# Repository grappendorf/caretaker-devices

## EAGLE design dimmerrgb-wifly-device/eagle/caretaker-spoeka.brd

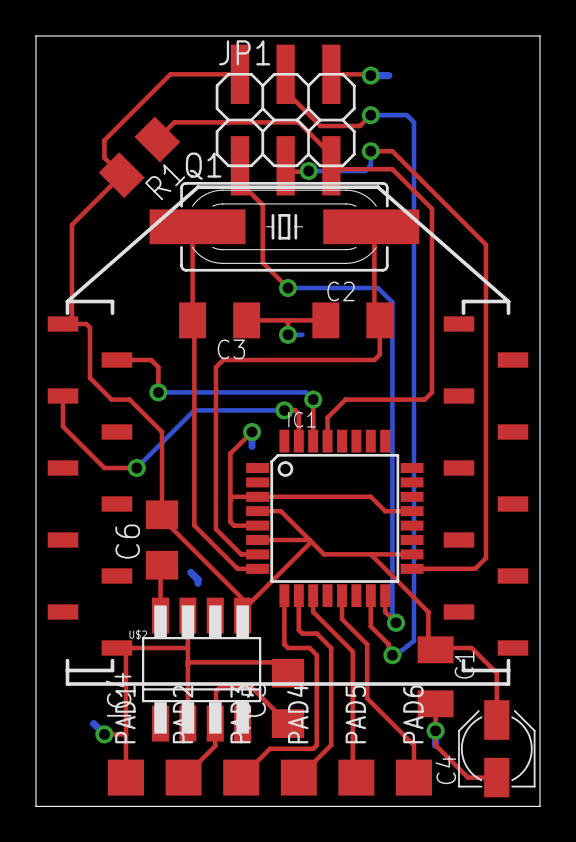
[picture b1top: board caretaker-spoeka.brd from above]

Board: 2 copper layers, 28.0 x 42.8 mm, 18 parts (0 on the bottom side), 16 nets.

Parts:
C1: 100n; C1206K
C2, C3: 22p; C1206K
C4: 1u/16V; PANASONIC_B
C5: 100n; C1206
C6: 10p; C1206
IC1: ATMEGA168; TQFP32-08
IC4: ZLDO330; SM8
JP1: 2X03SMD
PAD1, PAD2, PAD3, PAD4, PAD5, PAD6: PAD-SMD20S; SMD20S
Q1: 16MHz; HC49UP
R1: 10k; M1206
U$2: WIFLY-SMD

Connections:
+3V3: C1.1, C4.+, C6.2, IC1.4, IC1.6, IC1.18, IC4.5, JP1.2, R1.2, U$2.1
BUTTON: IC1.11, PAD5.PAD
GND: C1.2, C2.1, C3.1, C4.-, C5.2, IC1.3, IC1.5, IC1.21, IC4.2, IC4.7, JP1.6, PAD1.PAD, U$2.10
LED_BLUE: IC1.13, PAD6.PAD
LED_GREEN: IC1.10, PAD4.PAD
LED_RED: IC1.9, PAD3.PAD
MISO: IC1.16, JP1.1
MOSI: IC1.15, JP1.4
unnamed: C2.2, IC1.7, Q1.2
unnamed: C3.2, IC1.8, Q1.1
unnamed: C6.1, IC4.8
POW: C5.1, IC4.3, PAD2.PAD
RESET: IC1.29, JP1.5, R1.1
RXD: IC1.30, U$2.2
SCK: IC1.17, JP1.3
TXD: IC1.31, U$2.3

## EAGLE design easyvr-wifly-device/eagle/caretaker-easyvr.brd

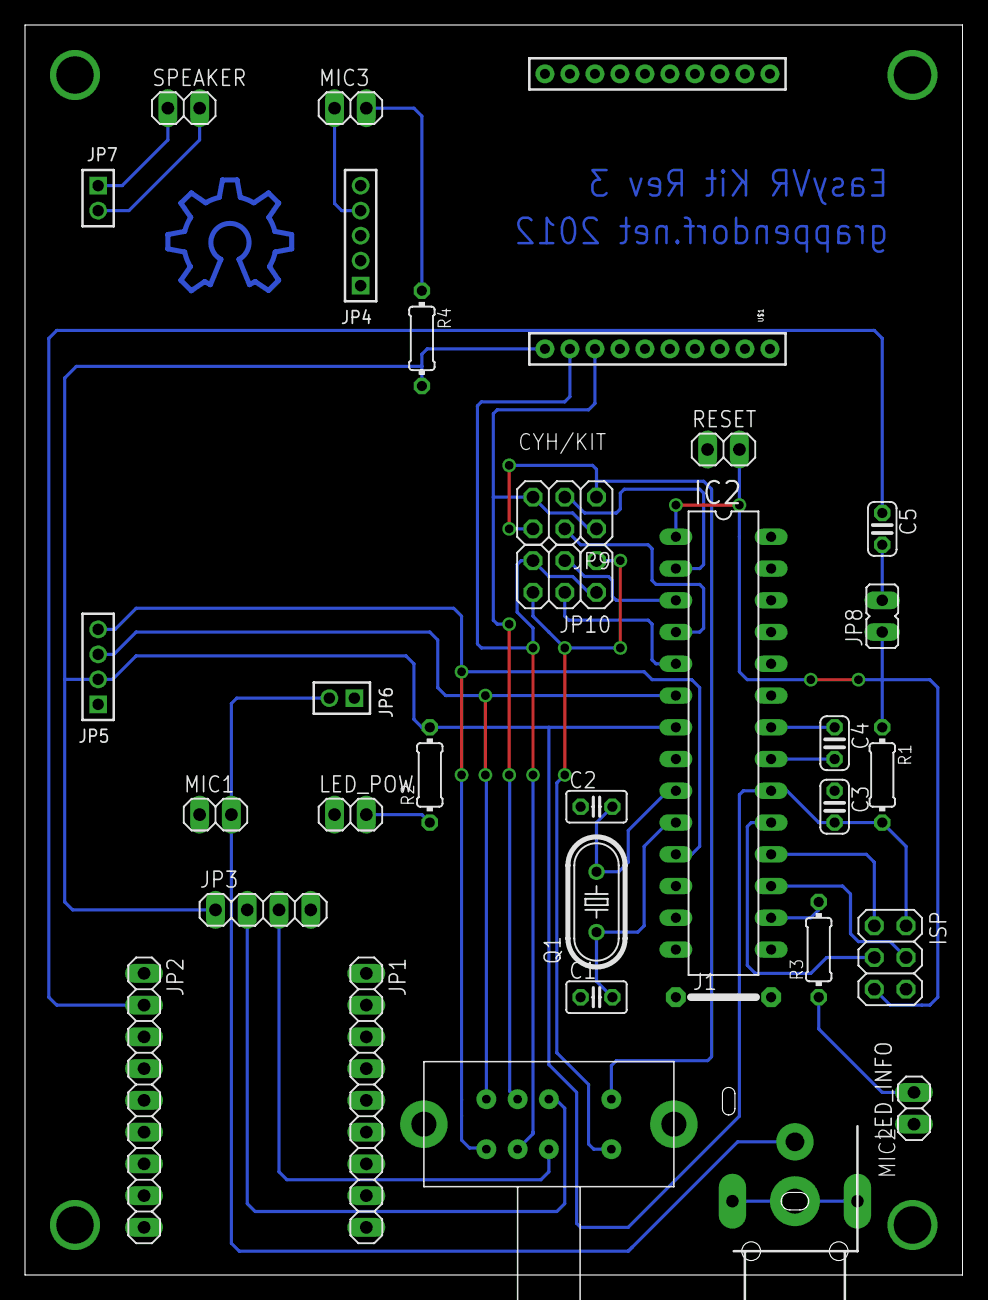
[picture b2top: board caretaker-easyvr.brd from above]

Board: 2 copper layers, 75.0 x 100.0 mm, 33 parts (0 on the bottom side), 31 nets.

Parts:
C1, C2: 22p; C025-025X050
C3, C4, C5: 100n; C025-024X044
IC2: ATmega168-20PU; DIL28-3
ISP: 2X03
J1: J7MM; 07
JP1, JP2: 1X09
JP3: 1X04
JP4: 1X05M
JP5: 1X04M
JP6, JP7: 1X02M
JP8: JP1
JP9, JP10: 2X03
LED_INFO: 1X02
LED_POW: 1X02
LOGO2: OSHW_LOGO_10MILX0350-NT-BOTTOM; OSHW_10X350_NOTEXT_BOTTOM
MIC1, MIC3: 1X02
MIC2: CINCH1
Q1: 16MHz; HC49U-V
R1: 10k; 0204/7
R2, R3: 1k; 0204/7
R4: 100; 0204/7
RESET: 1X02
SPEAKER: 1X02
U$1: WIFLY-TH
U$2: CONRAD-708038

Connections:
+3V3: C3.2, IC2.7, IC2.20, ISP.2, JP3.1, JP5.2, R1.2, R2.2, R4.2, U$1.1
AVR_RXD: JP9.1, JP9.6, U$2.C1
AVR_TXD: JP10.1, JP10.6, U$2.C2
EASYVR_RXD: IC2.6, JP5.3, U$2.A1
EASYVR_TXD: IC2.11, JP5.4, U$2.A2
GND: C1.1, C2.1, C3.1, C4.1, IC2.8, IC2.22, ISP.6, J1.1, J1.2, JP3.4, JP5.1, JP6.1, LED_INFO.1, LED_POW.1, MIC1.1, MIC2.T, MIC2.X1, MIC2.X2, RESET.1, U$1.10
LED_INFO: IC2.16, R3.2
MIC: JP6.2, MIC1.2, MIC2.S
unnamed: C2.2, IC2.9, Q1.2
unnamed: C1.2, IC2.10, Q1.1
unnamed: C4.2, IC2.21
unnamed: IC2.18, ISP.1
unnamed: IC2.19, ISP.3
unnamed: C5.2, JP8.2
unnamed: C5.1, JP2.2
unnamed: LED_POW.2, R2.1
unnamed: LED_INFO.2, R3.1
unnamed: JP7.2, SPEAKER.2
unnamed: JP7.1, SPEAKER.1
unnamed: JP4.4, MIC3.1
unnamed: MIC3.2, R4.1
unnamed: IC2.2, JP9.3
unnamed: IC2.4, JP9.4
unnamed: IC2.3, JP10.3
unnamed: IC2.5, JP10.4
unnamed: IC2.17, ISP.4
RESET: IC2.1, ISP.5, JP8.1, R1.1, RESET.2
USB_RXD: JP3.3, U$2.X2
USB_TXD: JP3.2, U$2.X1
WIFI_RXD: JP9.2, JP9.5, U$1.3, U$2.B1
WIFI_TXD: JP10.2, JP10.5, U$1.2, U$2.B2

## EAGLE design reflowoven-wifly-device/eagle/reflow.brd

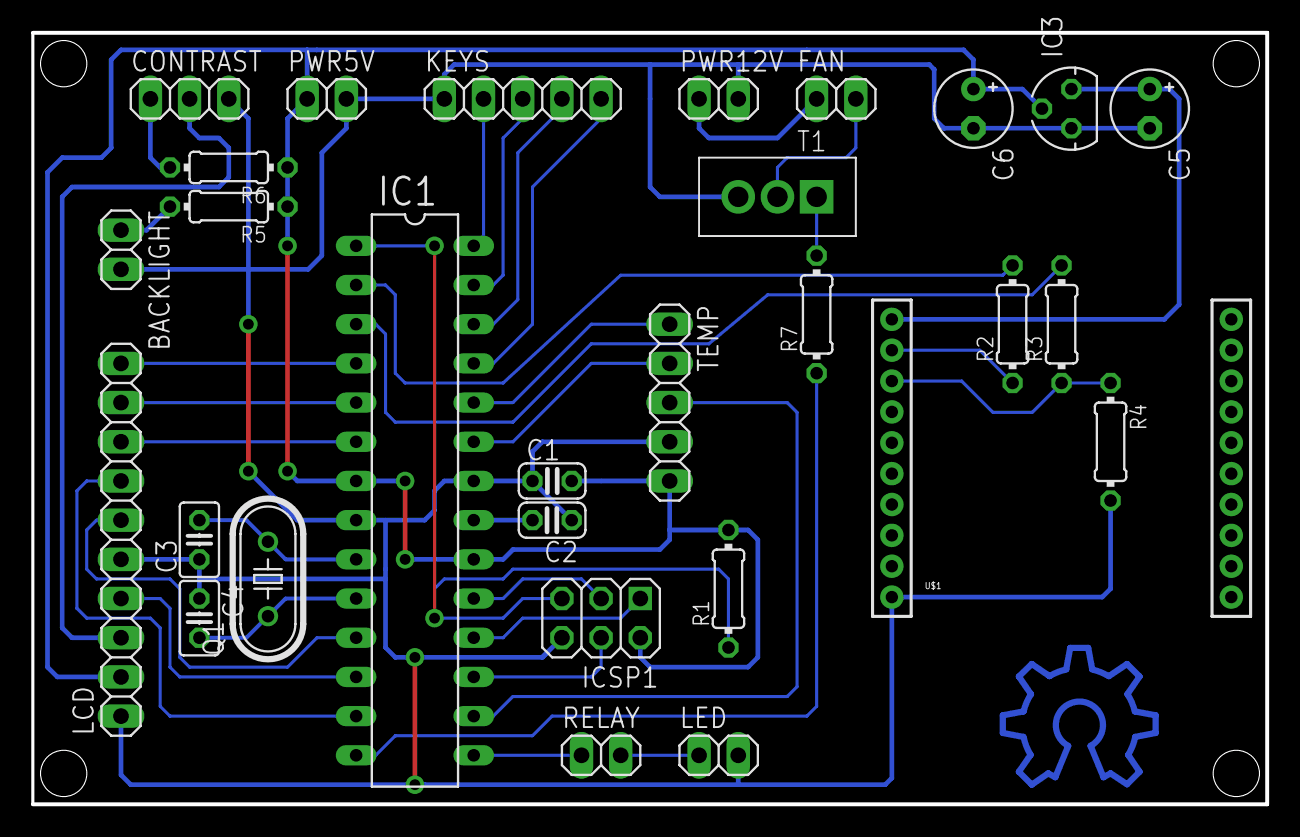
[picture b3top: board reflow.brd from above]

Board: 2 copper layers, 80.0 x 50.0 mm, 30 parts (0 on the bottom side), 36 nets.

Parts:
BACKLIGHT: 1X02
C1, C2: 100n; C025-024X044
C3, C4: 22p; C025-025X050
C5, C6: 1u; E2,5-5
CONTRAST: 1X03
FAN: 1X02
IC1: ATmega328P-20PU; DIL28-3
IC3: MCP1702-3302; MCP1702
ICSP1: 2X03
KEYS: 1X05
LCD: 1X10
LED: 1X02
LOGO1: OSHW_LOGO_10MILX0350-NT-BOTTOM; OSHW_10X350_NOTEXT_BOTTOM
PWR5V, PWR12V: 1X02
Q1: 16MHz; HC49U-V
R1, R6: 10k; 0204/7
R2, R3: 4k7; 0204/7
R4: 7k5; 0204/7
R5: 10; 0204/7
R7: 1k; 0204/7
RELAY: 1X02
T1: TIP110; T0220
TEMP: 1X05
U$1: WIFLY-TH

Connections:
+3V3: C5.+, IC3.VOUT, U$1.1
+5V: C1.2, C6.+, IC1.7, IC1.20, IC3.VIN, ICSP1.2, LCD.2, PWR5V.1, R1.2, R5.1, R6.1, TEMP.5
+12V: FAN.1, PWR12V.1
BUTTON1: IC1.25, KEYS.5
BUTTON2: IC1.26, KEYS.4
BUTTON3: IC1.27, KEYS.3
BUTTON4: IC1.28, KEYS.2
FAN: IC1.14, R7.1
GND: BACKLIGHT.2, C1.1, C2.1, C3.1, C4.1, C5.-, C6.-, CONTRAST.3, IC1.8, IC1.22, IC3.GND, ICSP1.6, KEYS.1, LCD.1, LCD.5, LED.2, PWR5V.2, PWR12V.2, R4.2, T1.3, TEMP.4, U$1.10
LCD_D4: IC1.13, LCD.7
LCD_D5: IC1.6, LCD.8
LCD_D6: IC1.5, LCD.9
LCD_D7: IC1.4, LCD.10
LCD_EN: IC1.11, LCD.6
LCD_RS: IC1.12, LCD.4
LCD_V0: CONTRAST.2, LCD.3
MISO: IC1.18, ICSP1.1
MOSI: IC1.17, ICSP1.4
unnamed: C3.2, IC1.9, Q1.2
unnamed: C4.2, IC1.10, Q1.1
unnamed: C2.2, IC1.21
unnamed: R3.1, R4.1, U$1.3
unnamed: R2.1, U$1.2
unnamed: BACKLIGHT.1, R5.2
unnamed: LED.1, RELAY.2
unnamed: CONTRAST.1, R6.2
unnamed: FAN.2, T1.2
unnamed: R7.2, T1.1
RELAY: IC1.15, RELAY.1
RESET: IC1.1, ICSP1.5, R1.1
RXD: IC1.2, R2.2
SCK: IC1.19, ICSP1.3
TEMP_CLK: IC1.24, TEMP.1
TEMP_CS: IC1.23, TEMP.2
TEMP_DO: IC1.16, TEMP.3
TXD: IC1.3, R3.2

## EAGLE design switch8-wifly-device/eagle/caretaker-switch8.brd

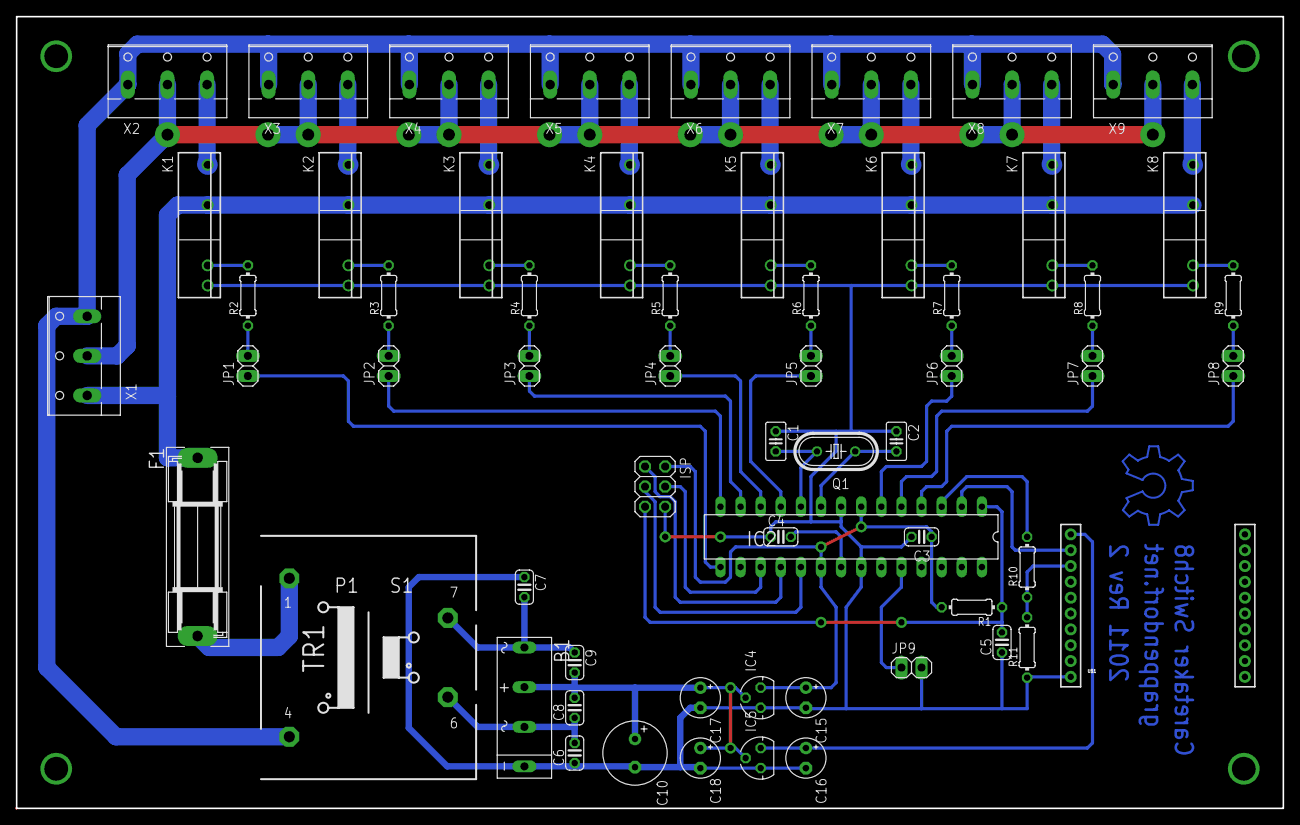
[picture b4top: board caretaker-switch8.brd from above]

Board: 2 copper layers, 160.0 x 100.0 mm, 61 parts (0 on the bottom side), 53 nets.

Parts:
B1: B40C1500; 2KBB
C1, C2: 22p; C025-025X050
C3, C4, C5: 100n; C025-024X044
C6, C7, C8, C9: 10n; C025-024X044
C10: 220u; E3,5-8
C15, C16, C17, C18: 1u; E2,5-5
F1: 2A; SH22,5
IC2: ATmega168-20PU; DIL28-3
IC4: MCP1702-5002; MCP1702
IC5: MCP1702-3302; MCP1702
ISP: 2X03
JP1: LED1; 1X02
JP2: LED2; 1X02
JP3: LED3; 1X02
JP4: LED4; 1X02
JP5: LED5; 1X02
JP6: LED6; 1X02
JP7: LED7; 1X02
JP8: LED8; 1X02
JP9: BUZZER; 1X02
K1, K2, K3, K4, K5, K6, K7, K8: S202S02
LOGO1: OSHW_LOGO_10MILX0350-NT-BOTTOM; OSHW_10X350_NOTEXT_BOTTOM
Q1: 16MHz; HC49U-V
R1, R10: 10k; 0204/7
R2, R3, R4, R5, R6, R7, R8, R9: 120; 0204/7
R11: 15k; 0204/7
TR1: TRAFO-1,0/1/6
U$1: WIFLY-TH
X1, X2, X3, X4, X5, X6, X7, X8, X9: W237-103

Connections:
+3V3: C16.+, IC5.VOUT, U$1.1
+5V: C3.2, C15.+, IC2.7, IC2.20, IC4.VOUT, ISP.2, R1.2
GND: B1.-, C1.1, C2.1, C3.1, C4.1, C5.1, C6.1, C7.1, C10.-, C15.-, C16.-, C17.-, C18.-, IC2.8, IC2.22, IC4.GND, IC5.GND, ISP.6, JP9.2, K1.4, K2.4, K3.4, K4.4, K5.4, K6.4, K7.4, K8.4, R11.1, U$1.10
unnamed: C2.2, IC2.9, Q1.2
unnamed: C1.2, IC2.10, Q1.1
unnamed: C4.2, IC2.21
unnamed: IC2.18, ISP.1
unnamed: IC2.24, JP9.1
unnamed: IC2.19, ISP.3
unnamed: K1.1, X2.3
unnamed: K2.1, X3.3
unnamed: K3.1, X4.3
unnamed: K4.1, X5.3
unnamed: B1.AC1, C7.2, C9.1, TR1.7
unnamed: K5.1, X6.3
unnamed: B1.+, C8.2, C9.2, C10.+, C17.+, C18.+, IC4.VIN, IC5.VIN
unnamed: K6.1, X7.3
unnamed: K7.1, X8.3
unnamed: K8.1, X9.3
unnamed: JP1.2, R2.1
unnamed: K1.3, R2.2
unnamed: JP2.2, R3.1
unnamed: K2.3, R3.2
unnamed: IC2.17, ISP.4
unnamed: JP3.2, R4.1
unnamed: K3.3, R4.2
unnamed: JP4.2, R5.1
unnamed: K4.3, R5.2
unnamed: JP5.2, R6.1
unnamed: K5.3, R6.2
unnamed: JP6.2, R7.1
unnamed: K6.3, R7.2
unnamed: JP7.2, R8.1
unnamed: K7.3, R8.2
unnamed: JP8.2, R9.1
unnamed: K8.3, R9.2
unnamed: F1.2, TR1.1
unnamed: R10.1, R11.2, U$1.3
unnamed: B1.AC2, C6.2, C8.1, TR1.6
POW-N: TR1.4, X1.3, X2.1, X3.1, X4.1, X5.1, X6.1, X7.1, X8.1, X9.1
POW-P: F1.1, K1.2, K2.2, K3.2, K4.2, K5.2, K6.2, K7.2, K8.2, X1.1
POW-S: X1.2, X2.2, X3.2, X4.2, X5.2, X6.2, X7.2, X8.2, X9.2
RESET: C5.2, IC2.1, ISP.5, R1.1
RXD: IC2.2, U$1.2
S1: IC2.15, JP1.1
S2: IC2.14, JP2.1
S3: IC2.13, JP3.1
S4: IC2.12, JP4.1
S5: IC2.11, JP5.1
S6: IC2.6, JP6.1
S7: IC2.5, JP7.1
S8: IC2.4, JP8.1
TXD: IC2.3, R10.2
